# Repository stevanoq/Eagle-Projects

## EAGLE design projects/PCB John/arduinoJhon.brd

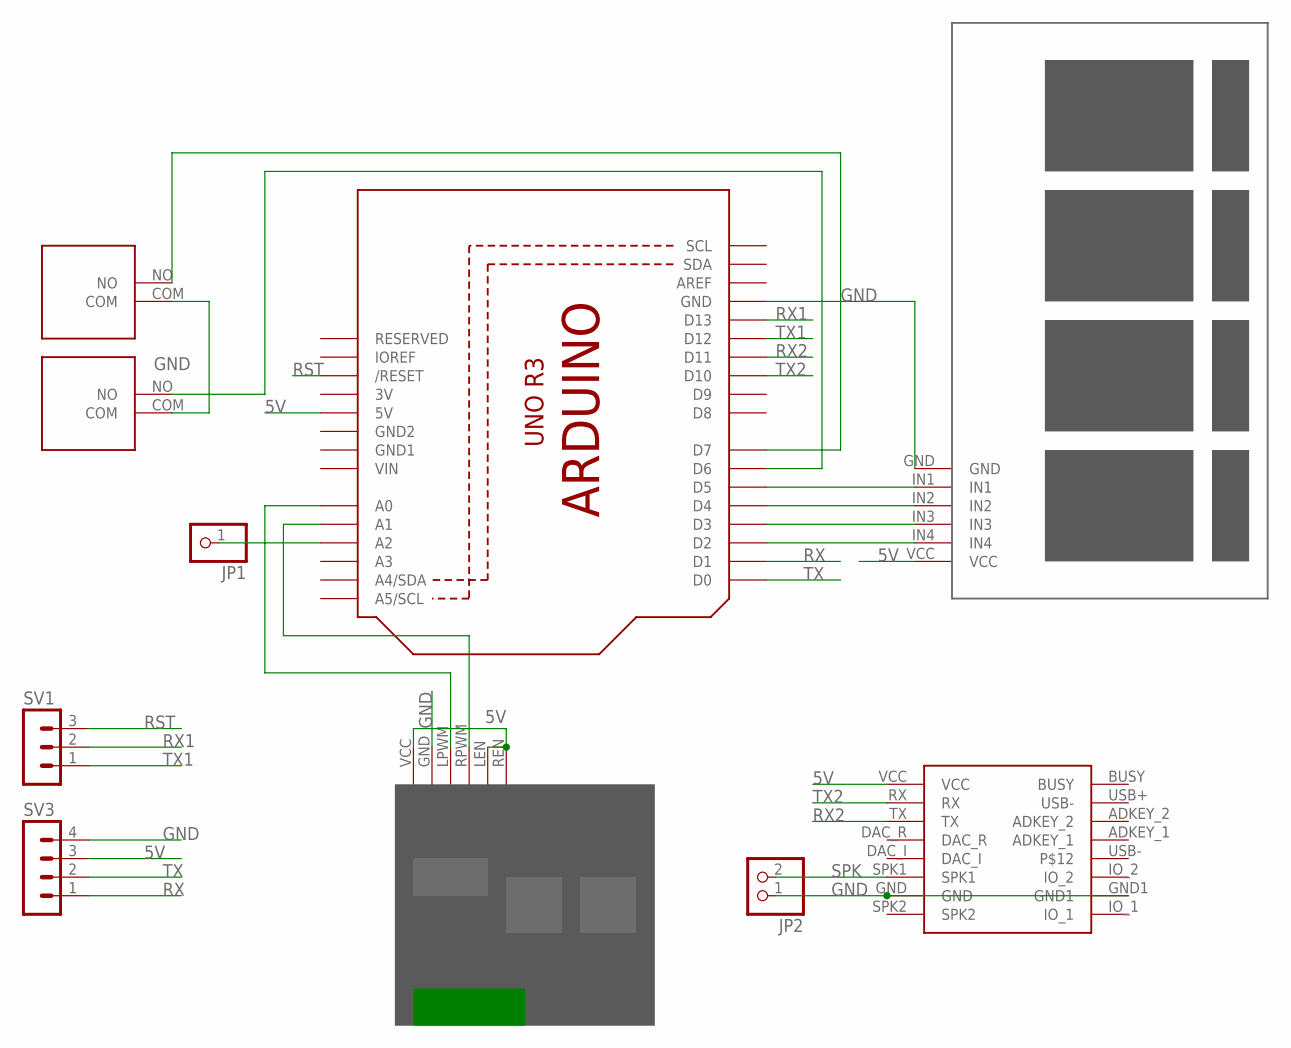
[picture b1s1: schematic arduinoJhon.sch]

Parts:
JP1: PINHD-1X1; 1X01
JP2: PINHD-1X2; 1X02
SV1: MA03-1
SV3: MA04-1
U$1: DFPLAYER_MINI
U$2: ARDUINO_UNO
U$9: RELAY_4CHANNEL
U$10: MOTOR_DRIVER_BTS7960
U$11, U$12: SWITCHLIMITER; SWICHLIMITER

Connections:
3V: U$2.3V
5V: SV3.3, U$1.VCC, U$2.5V, U$9.VCC, U$10.LEN, U$10.REN, U$10.VCC
GND: JP2.1, SV3.4, U$1.GND, U$1.GND1, U$2.GND, U$9.GND, U$10.GND, U$11.COM, U$12.COM
GND1: U$2.GND1
GND2: U$2.GND2
unnamed: JP1.1, U$2.A2
unnamed: U$2.D2, U$9.IN4
unnamed: U$2.D3, U$9.IN3
unnamed: U$2.D4, U$9.IN2
unnamed: U$2.D5, U$9.IN1
unnamed: U$2.D6, U$12.NO
unnamed: U$2.A0, U$10.LPWM
unnamed: U$2.A1, U$10.RPWM (RWM)
unnamed: U$2.D7, U$11.NO
RST: SV1.3, U$2.RESET (/RESET)
RX: SV3.1, U$2.D1
RX1: SV1.2, U$2.D13
RX2: U$1.TX, U$2.D11
SPK: JP2.2, U$1.SPK1
TX: SV3.2, U$2.D0
TX1: SV1.1, U$2.D12
TX2: U$1.RX, U$2.D10
VIN: U$2.VIN

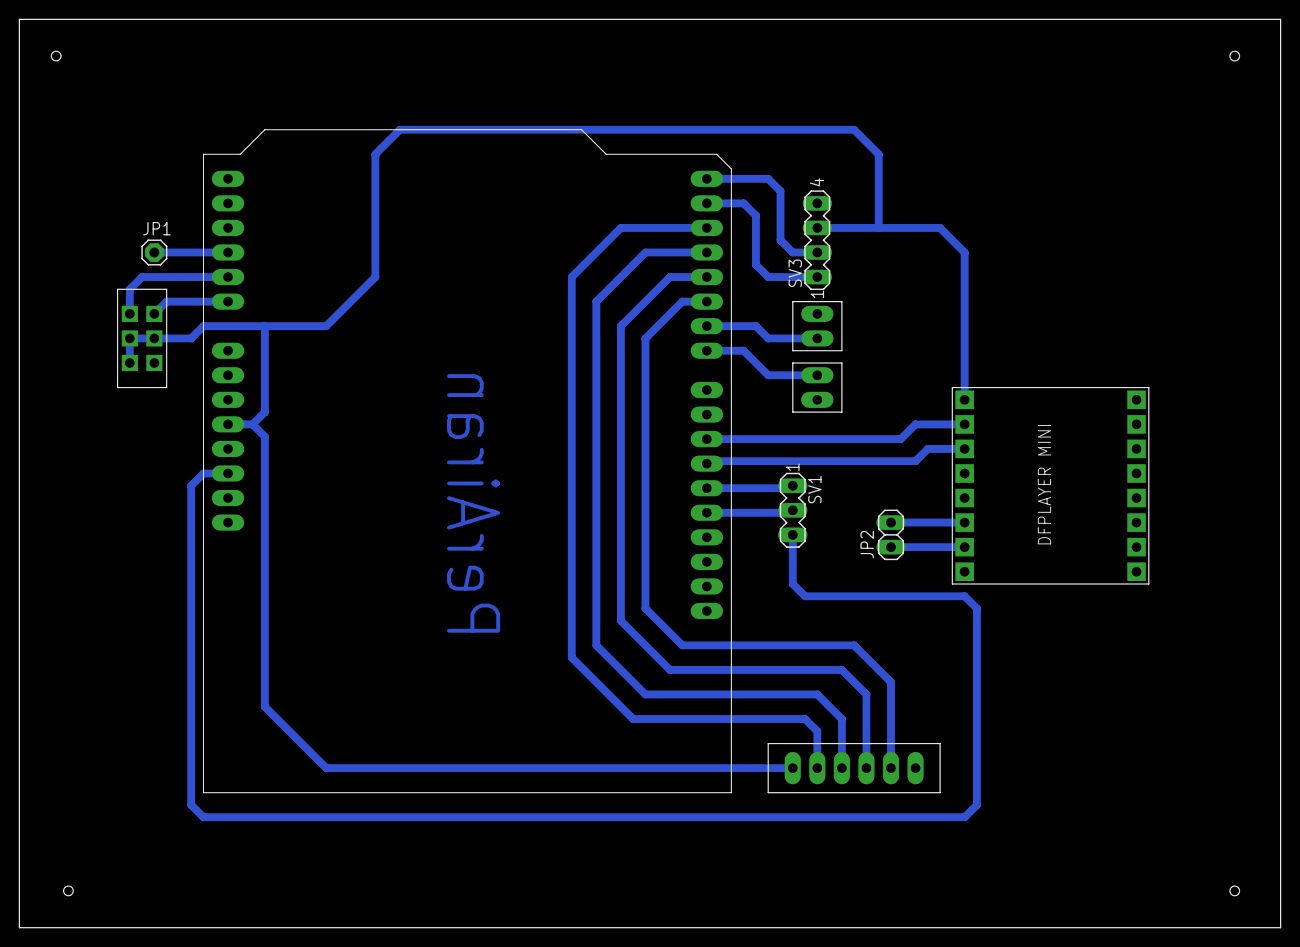
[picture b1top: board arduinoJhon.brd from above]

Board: 2 copper layers, 130.5 x 94.0 mm, 10 parts (0 on the bottom side), 19 nets.

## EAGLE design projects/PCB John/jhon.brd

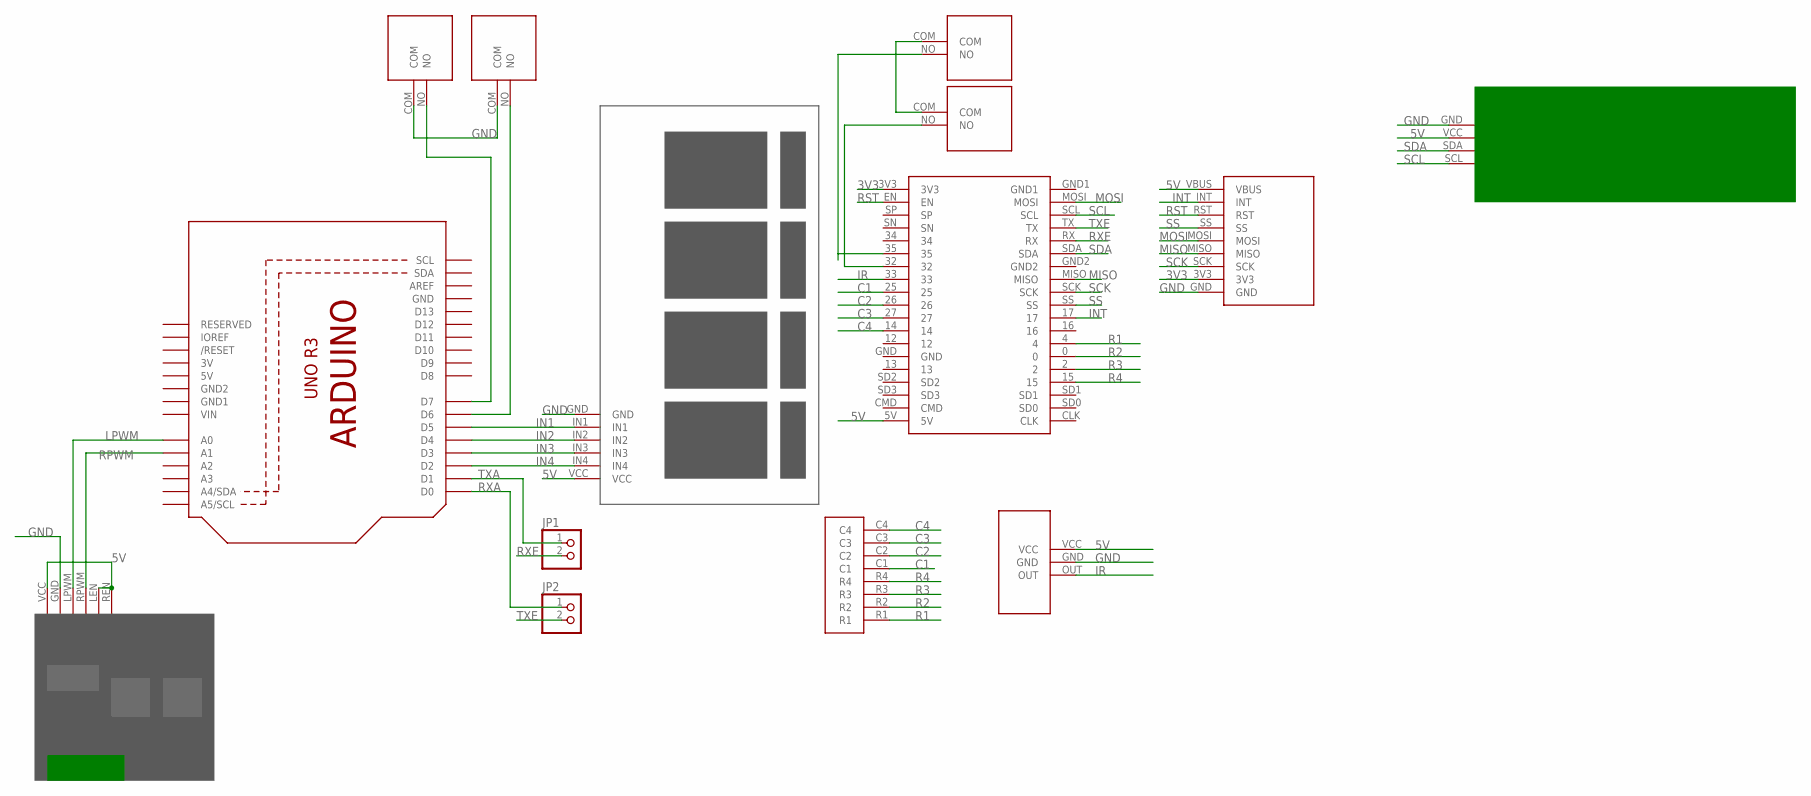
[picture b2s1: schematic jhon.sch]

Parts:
JP1, JP2: PINHD-1X2; 1X02
U$1: ARDUINO_UNO
U$2: ESP32_38PIN; ESP32
U$3: IR_SENSOR
U$4: KEYPAD
U$5: LCD_I2C
U$6: MOTOR_DRIVER_BTS7960
U$7: RELAY_4CHANNEL
U$8, U$9, U$10, U$11: SWITCHLIMITER; SWICHLIMITER
U$12: USB_HOST_SHIELD_2.0

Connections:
3V: U$1.3V
3V3: U$2.3V3, U$12.3V3
5V: U$1.5V, U$2.5V, U$3.VCC, U$5.VCC, U$6.LEN, U$6.REN, U$6.VCC, U$7.VCC, U$12.VBUS
C1: U$2.25, U$4.C1
C2: U$2.26, U$4.C2
C3: U$2.27, U$4.C3
C4: U$2.14, U$4.C4
GND: U$1.GND, U$3.GND, U$5.GND, U$6.GND, U$7.GND, U$10.COM, U$11.COM, U$12.GND
GND1: U$1.GND1
GND2: U$1.GND2
IN1: U$1.D5, U$7.IN1
IN2: U$1.D4, U$7.IN2
IN3: U$1.D3, U$7.IN3
IN4: U$1.D2, U$7.IN4
INT: U$2.17, U$12.INT
IR: U$2.33, U$3.OUT
LPWM: U$1.A0, U$6.LPWM
MISO: U$2.MISO, U$12.MISO
MOSI: U$2.MOSI, U$12.MOSI
unnamed: U$8.COM, U$9.COM
unnamed: U$1.D6, U$10.NO
unnamed: U$1.D7, U$11.NO
unnamed: U$2.32, U$9.NO
unnamed: U$2.35, U$8.NO
R1: U$2.4, U$4.R1
R2: U$2.0, U$4.R2
R3: U$2.2, U$4.R3
R4: U$2.15, U$4.R4
RPWM: U$1.A1, U$6.RPWM (RWM)
RST: U$2.EN, U$12.RST
RXA: JP2.1, U$1.D0
RXE: JP1.2, U$2.RX
SCK: U$2.SCK, U$12.SCK
SCL: U$2.SCL, U$5.SCL
SDA: U$2.SDA, U$5.SDA
SS: U$2.SS, U$12.SS
TXA: JP1.1, U$1.D1
TXE: JP2.2, U$2.TX
VIN: U$1.VIN

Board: 2 copper layers, 14 parts (0 on the bottom side), 35 nets, no tracks yet.

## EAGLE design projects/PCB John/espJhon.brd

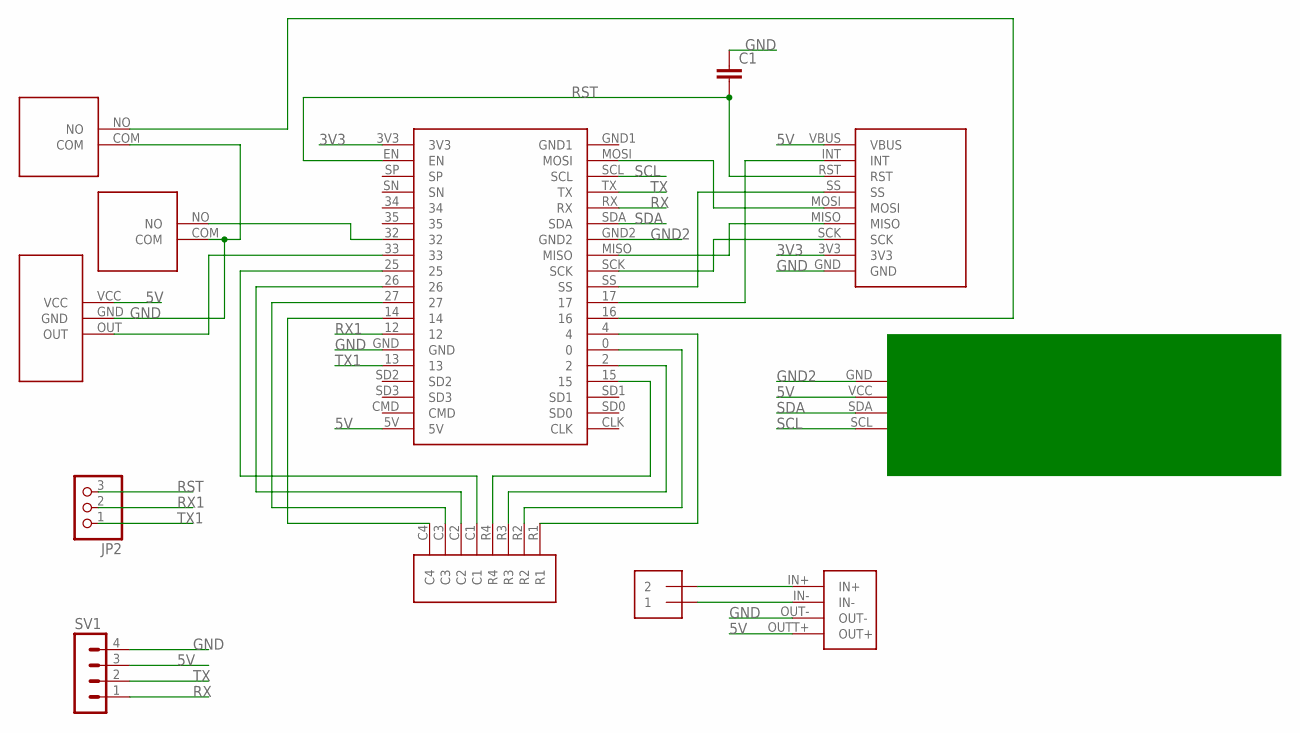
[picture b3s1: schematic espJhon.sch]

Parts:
C1: C2.5/6; C2.5-6
J1: 1X2-3.5MM
JP2: PINHD-1X3; 1X03
SV1: MA04-1
U$1: XL4005E1
U$2: USB_HOST
U$3: ESP32_NEW
U$4: KEYPAD_4X4
U$6: LCD_I2C
U$7: IR_SENSOR
U$8, U$9: SWITCHLIMITER; SWICHLIMITER

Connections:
3V3: U$2.3V3, U$3.3V3
5V: SV1.3, U$1.OUTT+ (OUT+), U$2.VBUS, U$3.5V, U$6.VCC, U$7.VCC
GND: C1.1, SV1.4, U$1.OUT-, U$2.GND, U$3.GND, U$7.GND, U$8.COM, U$9.COM
GND2: U$3.GND2, U$6.GND
unnamed: J1.2, U$1.IN+
unnamed: J1.1, U$1.IN-
unnamed: U$3.14, U$4.C4
unnamed: U$3.27, U$4.C3
unnamed: U$3.26, U$4.C2
unnamed: U$3.25, U$4.C1
unnamed: U$3.15, U$4.R4
unnamed: U$3.2, U$4.R3
unnamed: U$3.0, U$4.R2
unnamed: U$3.4, U$4.R1
unnamed: U$2.MOSI, U$3.MOSI
unnamed: U$2.MISO, U$3.MISO
unnamed: U$2.SCK, U$3.SCK
unnamed: U$2.SS, U$3.SS
unnamed: U$2.INT, U$3.17
unnamed: U$3.33, U$7.OUT
unnamed: U$3.32, U$9.NO
unnamed: U$3.16, U$8.NO
RST: C1.2, JP2.3, U$2.RST, U$3.EN
RX: SV1.1, U$3.RX
RX1: JP2.2, U$3.12
SCL: U$3.SCL, U$6.SCL
SDA: U$3.SDA, U$6.SDA
TX: SV1.2, U$3.TX
TX1: JP2.1, U$3.13

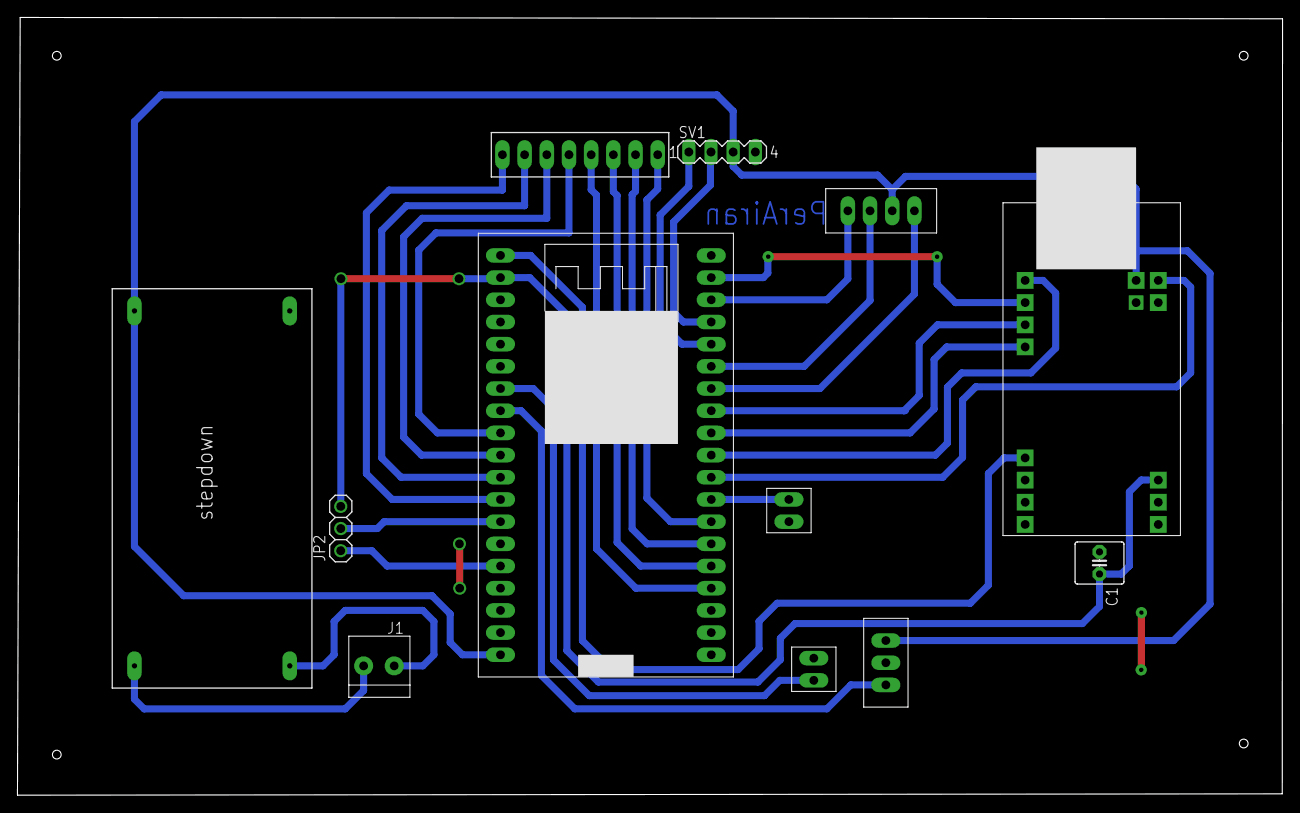
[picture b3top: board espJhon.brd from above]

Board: 2 copper layers, 144.8 x 89.0 mm, 12 parts (0 on the bottom side), 29 nets.

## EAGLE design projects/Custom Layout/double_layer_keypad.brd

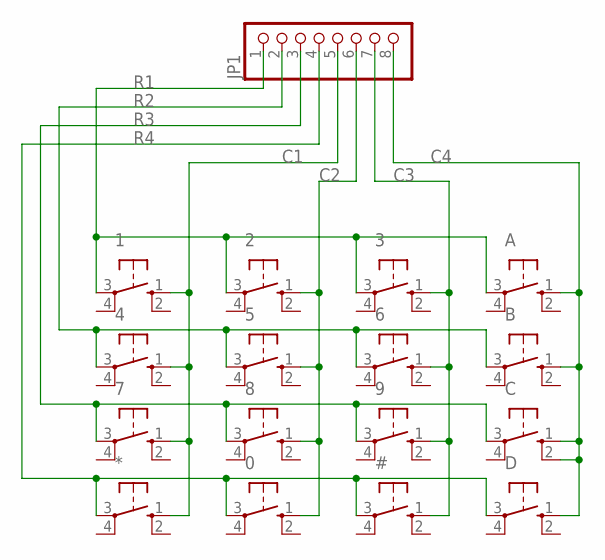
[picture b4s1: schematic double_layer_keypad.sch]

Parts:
0, 1, 2, 3, 4, 5, 6, 7, 8, 9: 10-XX; B3F-10XX
#: 10-XX; B3F-10XX
*: 10-XX; B3F-10XX
A: 10-XX; B3F-10XX
B: 10-XX; B3F-10XX
C: 10-XX; B3F-10XX
D: 10-XX; B3F-10XX
JP1: PINHD-1X8; 1X08

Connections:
C1: 1.1 (S), 4.1 (S), 7.1 (S), *.1 (S), JP1.5
C2: 0.1 (S), 2.1 (S), 5.1 (S), 8.1 (S), JP1.6
C3: 3.1 (S), 6.1 (S), 9.1 (S), #.1 (S), JP1.7
C4: A.1 (S), B.1 (S), C.1 (S), C.2 (S1), D.1 (S), JP1.8
R1: 1.3, 2.3, 3.3, A.3, JP1.1
R2: 4.3, 5.3, 6.3, B.3, JP1.2
R3: 7.3, 8.3, 9.3, C.3, JP1.3
R4: 0.3, #.3, *.3, D.3, JP1.4

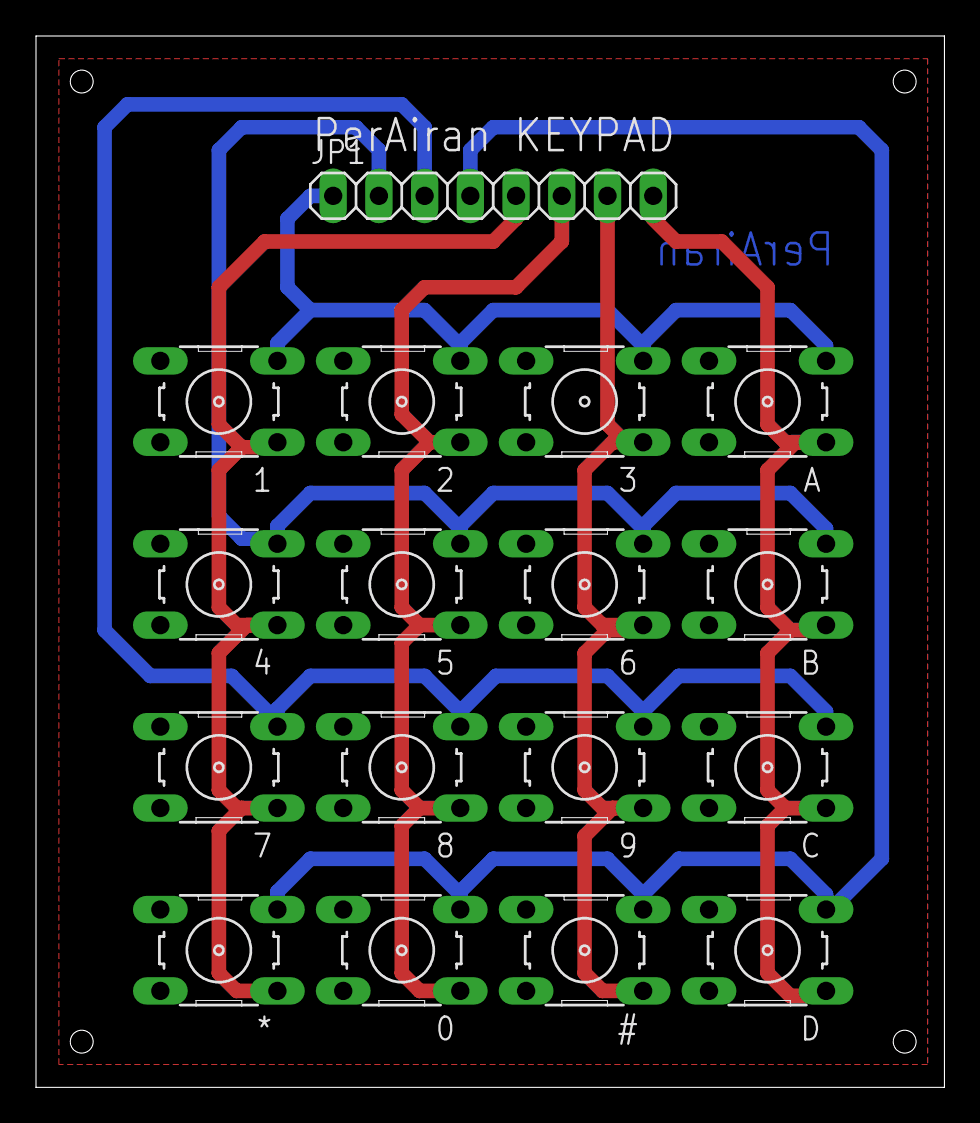
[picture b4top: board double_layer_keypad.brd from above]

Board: 2 copper layers, 50.5 x 58.4 mm, 17 parts (0 on the bottom side), 8 nets.

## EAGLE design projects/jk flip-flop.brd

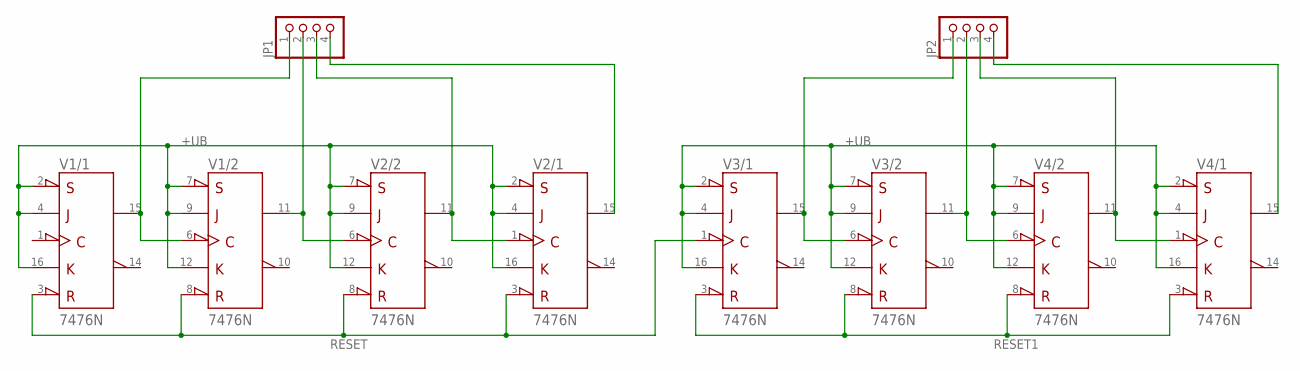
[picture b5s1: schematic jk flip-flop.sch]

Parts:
JP1, JP2: PINHD-1X4; 1X04
V1, V2, V3, V4: 7476N; DIL16

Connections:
+UB: V1.2 (!PRE), V1.4 (J), V1.5 (+UB), V1.7 (!PRE), V1.9 (J), V1.12 (K), V1.16 (K), V2.2 (!PRE), V2.4 (J), V2.5 (+UB), V2.7 (!PRE), V2.9 (J), V2.12 (K), V2.16 (K), V3.2 (!PRE), V3.4 (J), V3.5 (+UB), V3.7 (!PRE), V3.9 (J), V3.12 (K), V3.16 (K), V4.2 (!PRE), V4.4 (J), V4.5 (+UB), V4.7 (!PRE), V4.9 (J), V4.12 (K), V4.16 (K)
-UB: V1.13 (-UB), V2.13 (-UB), V3.13 (-UB), V4.13 (-UB)
unnamed: JP2.1, V3.6 (CLK), V3.15 (Q)
unnamed: JP2.2, V3.11 (Q), V4.6 (CLK)
unnamed: JP1.4, V2.15 (Q)
unnamed: JP1.1, V1.6 (CLK), V1.15 (Q)
unnamed: JP1.2, V1.11 (Q), V2.6 (CLK)
unnamed: JP1.3, V2.1 (CLK), V2.11 (Q)
unnamed: JP2.3, V4.1 (CLK), V4.11 (Q)
unnamed: JP2.4, V4.15 (Q)
RESET: V1.3 (!CLR), V1.8 (!CLR), V2.3 (!CLR), V2.8 (!CLR), V3.1 (CLK)
RESET1: V3.3 (!CLR), V3.8 (!CLR), V4.3 (!CLR), V4.8 (!CLR)

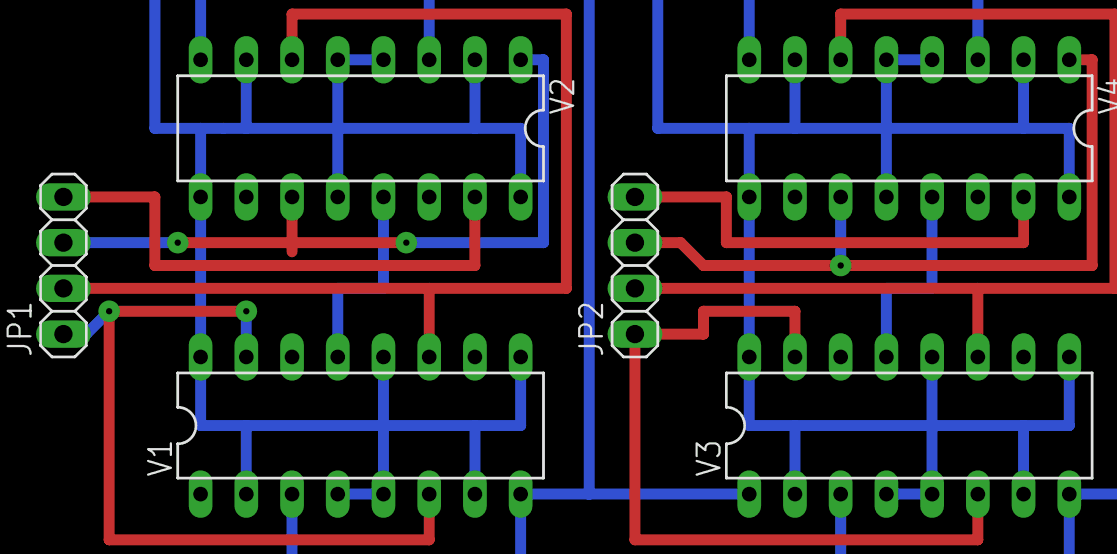
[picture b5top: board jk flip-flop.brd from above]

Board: 2 copper layers, 6 parts (0 on the bottom side), 12 nets.

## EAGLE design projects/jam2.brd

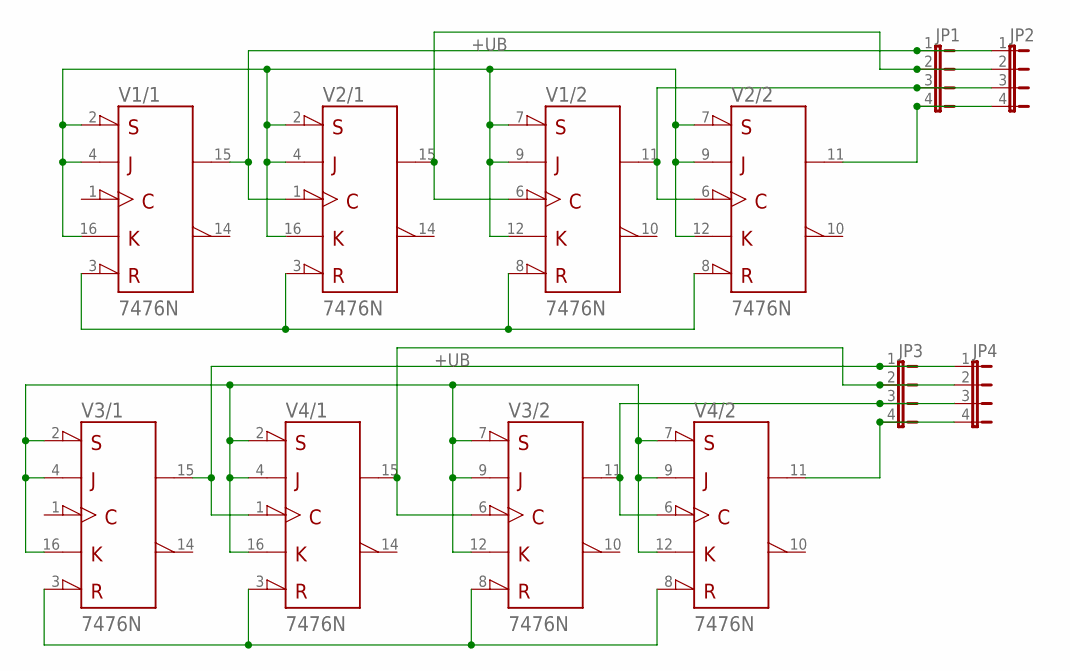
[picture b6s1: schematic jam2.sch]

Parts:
JP1, JP2, JP3, JP4: JP4E; JP4
V1, V2, V3, V4: 7476N; DIL16

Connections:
+UB: V1.2 (!PRE), V1.4 (J), V1.5 (+UB), V1.7 (!PRE), V1.9 (J), V1.12 (K), V1.16 (K), V2.2 (!PRE), V2.4 (J), V2.5 (+UB), V2.7 (!PRE), V2.9 (J), V2.12 (K), V2.16 (K), V3.2 (!PRE), V3.4 (J), V3.5 (+UB), V3.7 (!PRE), V3.9 (J), V3.12 (K), V3.16 (K), V4.2 (!PRE), V4.4 (J), V4.5 (+UB), V4.7 (!PRE), V4.9 (J), V4.12 (K), V4.16 (K)
-UB: V1.13 (-UB), V2.13 (-UB), V3.13 (-UB), V4.13 (-UB)
unnamed: JP1.4, JP2.4, V2.11 (Q)
unnamed: JP1.3, JP2.3, V1.11 (Q), V2.6 (CLK)
unnamed: JP1.2, JP2.2, V1.6 (CLK), V2.15 (Q)
unnamed: V3.3 (!CLR), V3.8 (!CLR), V4.3 (!CLR), V4.8 (!CLR)
unnamed: JP3.3, JP4.3, V3.11 (Q), V4.6 (CLK)
unnamed: JP1.1, JP2.1, V1.15 (Q), V2.1 (CLK)
unnamed: JP3.2, JP4.2, V3.6 (CLK), V4.15 (Q)
unnamed: V1.3 (!CLR), V1.8 (!CLR), V2.3 (!CLR), V2.8 (!CLR)
unnamed: JP3.4, JP4.4, V4.11 (Q)
unnamed: JP3.1, JP4.1, V3.15 (Q), V4.1 (CLK)

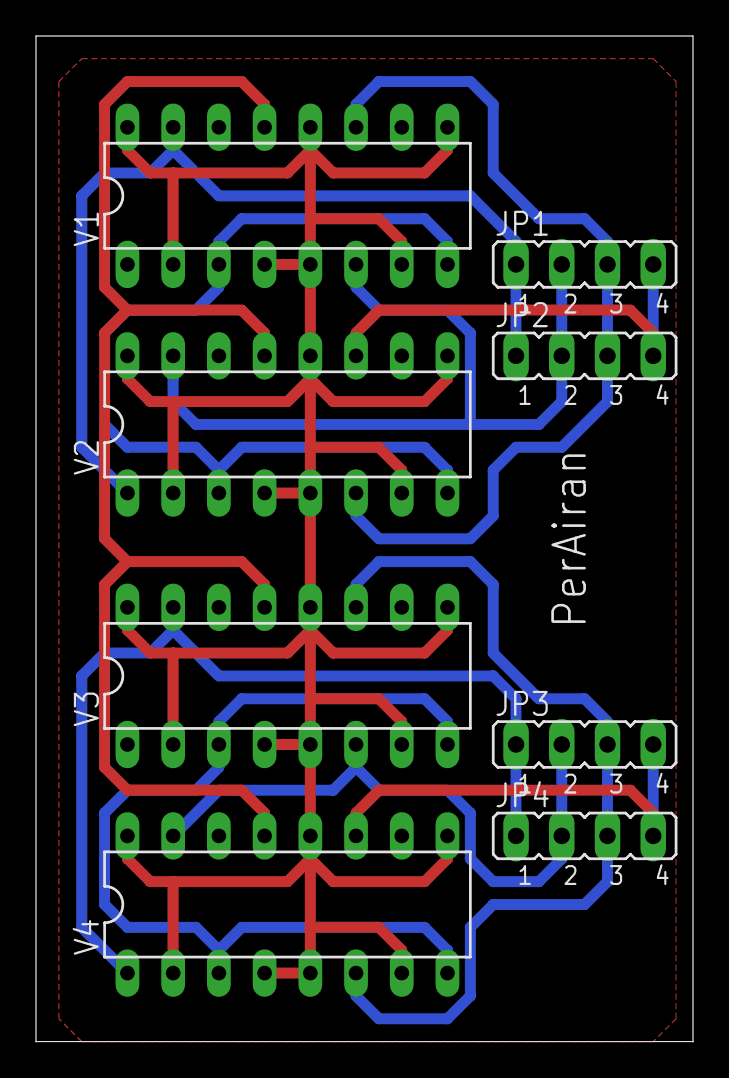
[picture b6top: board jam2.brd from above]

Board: 2 copper layers, 36.5 x 55.9 mm, 8 parts (0 on the bottom side), 12 nets.

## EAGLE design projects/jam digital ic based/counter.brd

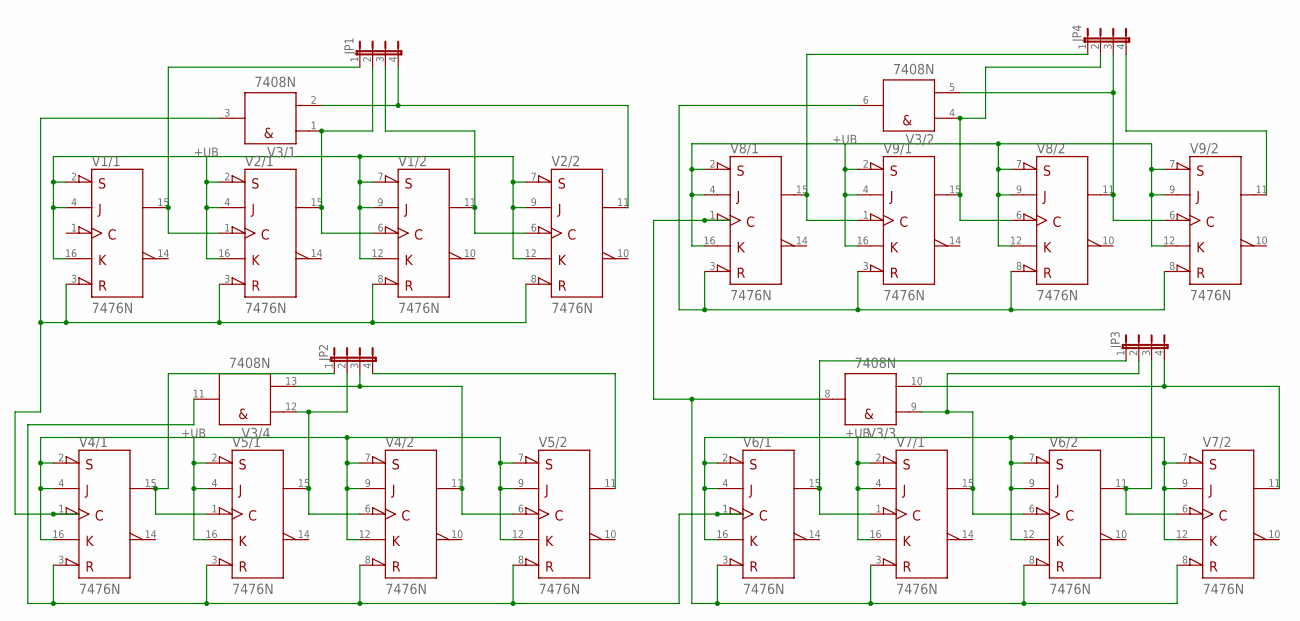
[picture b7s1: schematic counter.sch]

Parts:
JP1, JP2, JP3, JP4: JP4E; JP4
V1, V2, V4, V5, V6, V7, V8, V9: 7476N; DIL16
V3: 7408N; DIL14

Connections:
+UB: V1.2 (!PRE), V1.4 (J), V1.5 (+UB), V1.7 (!PRE), V1.9 (J), V1.12 (K), V1.16 (K), V2.2 (!PRE), V2.4 (J), V2.5 (+UB), V2.7 (!PRE), V2.9 (J), V2.12 (K), V2.16 (K), V3.14 (+UB), V4.2 (!PRE), V4.4 (J), V4.5 (+UB), V4.7 (!PRE), V4.9 (J), V4.12 (K), V4.16 (K), V5.2 (!PRE), V5.4 (J), V5.5 (+UB), V5.7 (!PRE), V5.9 (J), V5.12 (K), V5.16 (K), V6.2 (!PRE), V6.4 (J), V6.5 (+UB), V6.7 (!PRE), V6.9 (J), V6.12 (K), V6.16 (K), V7.2 (!PRE), V7.4 (J), V7.5 (+UB), V7.7 (!PRE), V7.9 (J), V7.12 (K), V7.16 (K), V8.2 (!PRE), V8.4 (J), V8.5 (+UB), V8.7 (!PRE), V8.9 (J), V8.12 (K), V8.16 (K), V9.2 (!PRE), V9.4 (J), V9.5 (+UB), V9.7 (!PRE), V9.9 (J), V9.12 (K), V9.16 (K)
-UB: V1.13 (-UB), V2.13 (-UB), V3.7 (-UB), V4.13 (-UB), V5.13 (-UB), V6.13 (-UB), V7.13 (-UB), V8.13 (-UB), V9.13 (-UB)
unnamed: JP1.1, V1.15 (Q), V2.1 (CLK)
unnamed: JP1.2, V1.6 (CLK), V2.15 (Q), V3.1 (A)
unnamed: V1.3 (!CLR), V1.8 (!CLR), V2.3 (!CLR), V2.8 (!CLR), V3.3 (Y), V4.1 (CLK)
unnamed: JP1.3, V1.11 (Q), V2.6 (CLK)
unnamed: JP1.4, V2.11 (Q), V3.2 (B)
unnamed: JP3.4, V3.10 (B), V7.11 (Q)
unnamed: V3.11 (Y), V4.3 (!CLR), V4.8 (!CLR), V5.3 (!CLR), V5.8 (!CLR), V6.1 (CLK)
unnamed: JP2.1, V4.15 (Q), V5.1 (CLK)
unnamed: JP2.2, V3.12 (A), V4.6 (CLK), V5.15 (Q)
unnamed: JP2.3, V3.13 (B), V4.11 (Q), V5.6 (CLK)
unnamed: JP2.4, V5.11 (Q)
unnamed: V3.6 (Y), V8.3 (!CLR), V8.8 (!CLR), V9.3 (!CLR), V9.8 (!CLR)
unnamed: V3.8 (Y), V6.3 (!CLR), V6.8 (!CLR), V7.3 (!CLR), V7.8 (!CLR), V8.1 (CLK)
unnamed: JP3.1, V6.15 (Q), V7.1 (CLK)
unnamed: JP3.2, V3.9 (A), V6.6 (CLK), V7.15 (Q)
unnamed: JP3.3, V6.11 (Q), V7.6 (CLK)
unnamed: JP4.1, V8.15 (Q), V9.1 (CLK)
unnamed: JP4.4, V9.11 (Q)
unnamed: JP4.3, V3.5 (B), V8.11 (Q), V9.6 (CLK)
unnamed: JP4.2, V3.4 (A), V8.6 (CLK), V9.15 (Q)

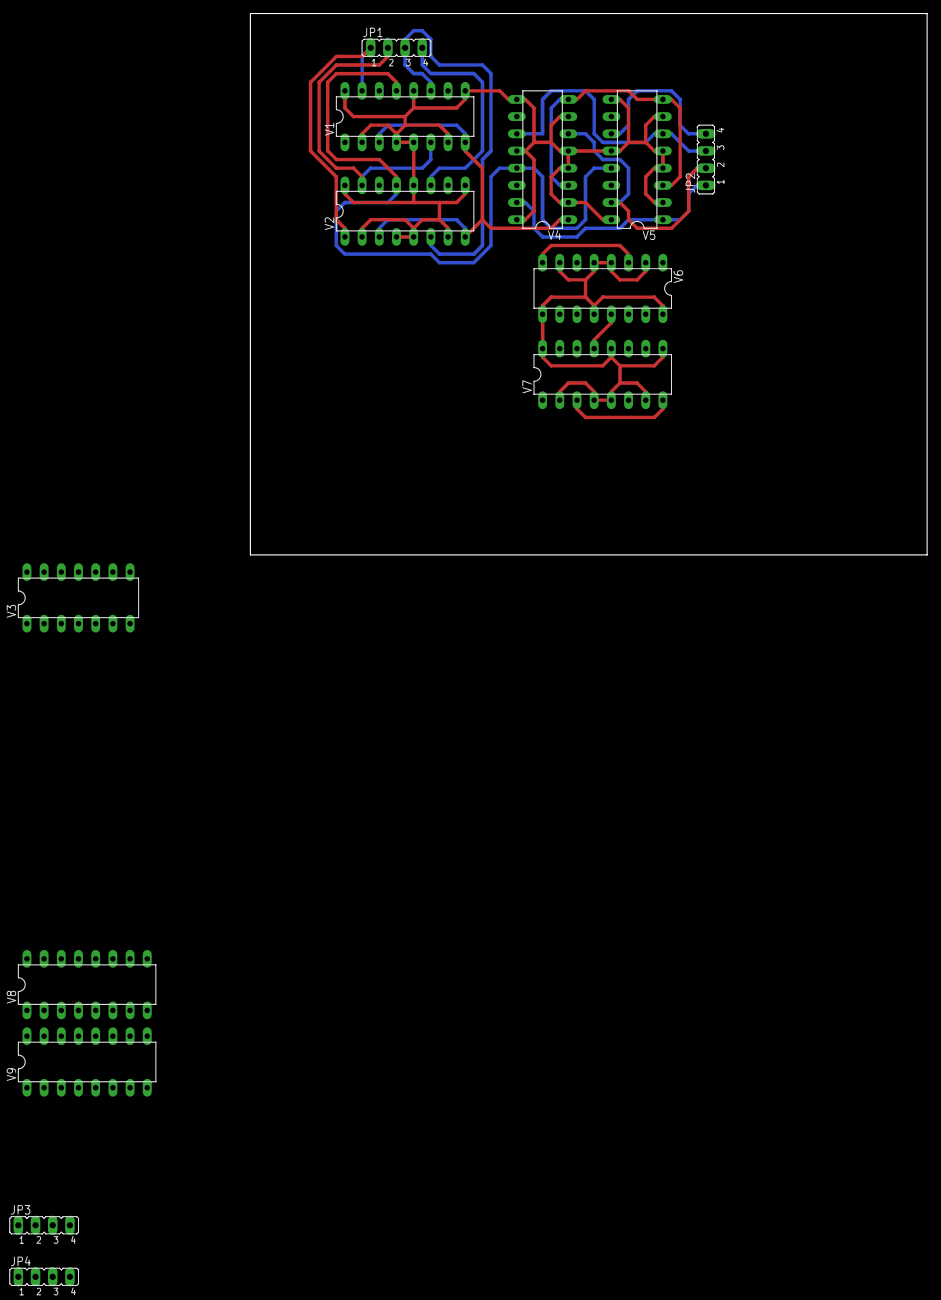
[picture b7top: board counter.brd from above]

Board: 2 copper layers, 100.0 x 80.0 mm, 13 parts (0 on the bottom side), 22 nets.

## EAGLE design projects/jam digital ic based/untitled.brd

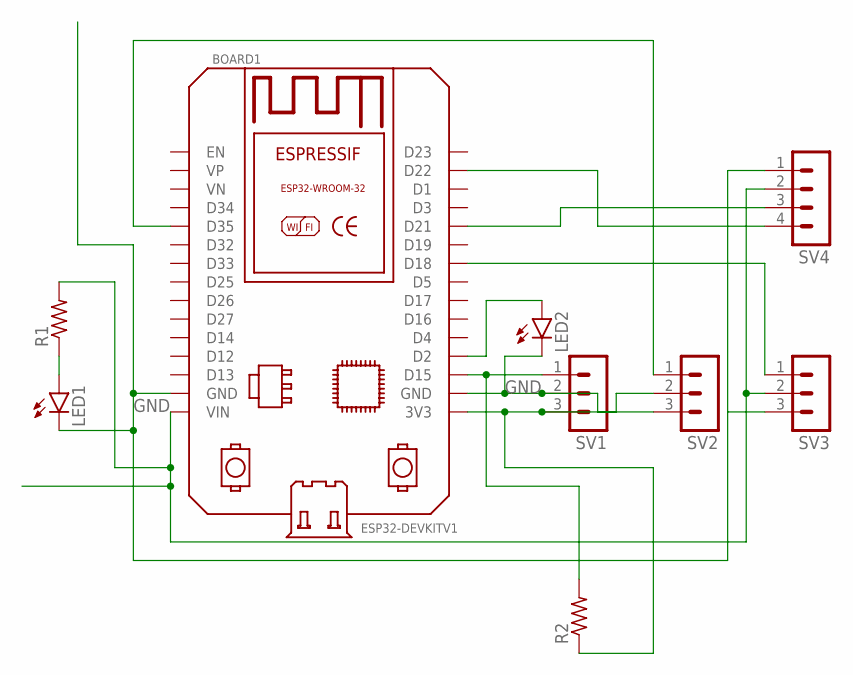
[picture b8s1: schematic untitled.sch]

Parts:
BOARD1: ESP32DEVKITV1; ESP32-DEVKITV1
LED1, LED2: LED5MM
R1, R2: R-US_0204/7; 0204/7
SV1, SV2, SV3: MA03-1
SV4: MA04-1

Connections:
GND: BOARD1.GND, BOARD1.GND@1 (GND), LED1.K (C), LED2.K (C), SV1.2, SV2.3, SV3.3, SV4.1
unnamed: BOARD1.3V3, R2.1, SV1.3, SV2.2
unnamed: BOARD1.D15, R2.2, SV1.1
unnamed: BOARD1.D18, SV3.1
unnamed: LED1.A, R1.1
unnamed: BOARD1.D21, SV4.3
unnamed: BOARD1.D22, SV4.4
unnamed: BOARD1.D35, SV2.1
unnamed: BOARD1.D2, LED2.A
unnamed: BOARD1.VIN, R1.2, SV3.2, SV4.2

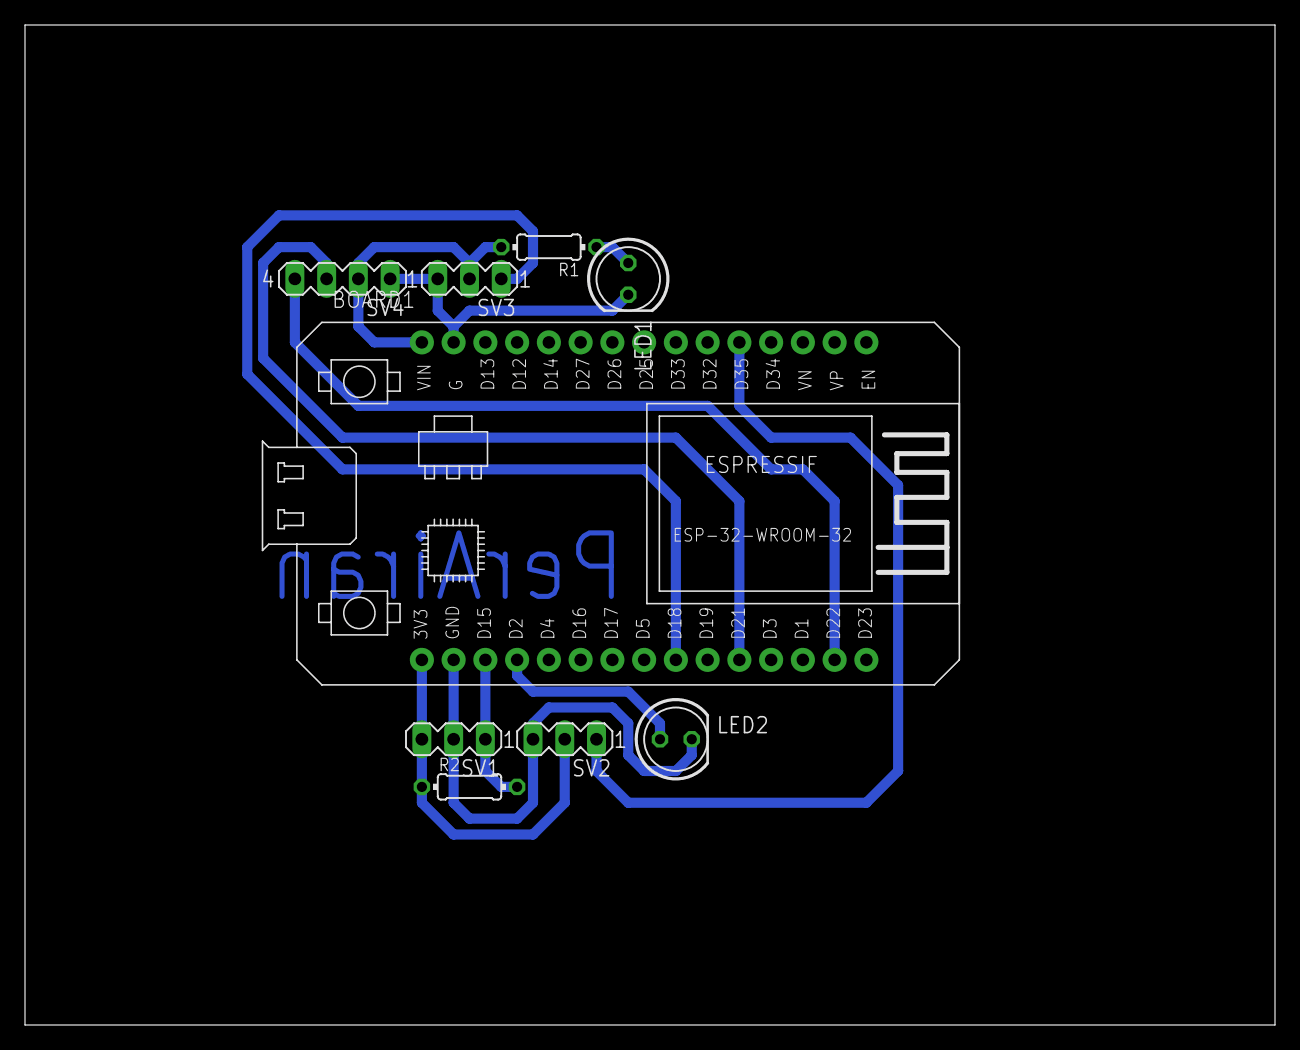
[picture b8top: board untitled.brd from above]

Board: 2 copper layers, 100.0 x 80.0 mm, 9 parts (0 on the bottom side), 10 nets.

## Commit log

2023-02-24 new upload
2023-02-24 upload libraries
2023-07-05 update from tiara's laptop
